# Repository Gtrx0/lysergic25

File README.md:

# Lysergic 25
5x5 Macropad PCB

# [Layout](http://www.keyboard-layout-editor.com/#/gists/2997f919e892d07fd131f2b731a871e9)

## Features
* In-switch LED support.
* Individually addressible RGB underglow provided by 8 separate WS2812B LEDs.
* USB micro B to USB type-C converter which works like the one ergodox, so no more ripped off usb ports on your pro micro.
* Compatible with Cherry MX ALPS and Kailh CHOC switches. 
* Pro Micro microcontroller for easy diy assembly.
* USB ESD protection circuit.
* 0805 SMD and through hole Diode/resistor compatibility for ease of assembly.

## Warning
KiCad 5 or above is needed to open this project. KiCad 4 or below won't work.

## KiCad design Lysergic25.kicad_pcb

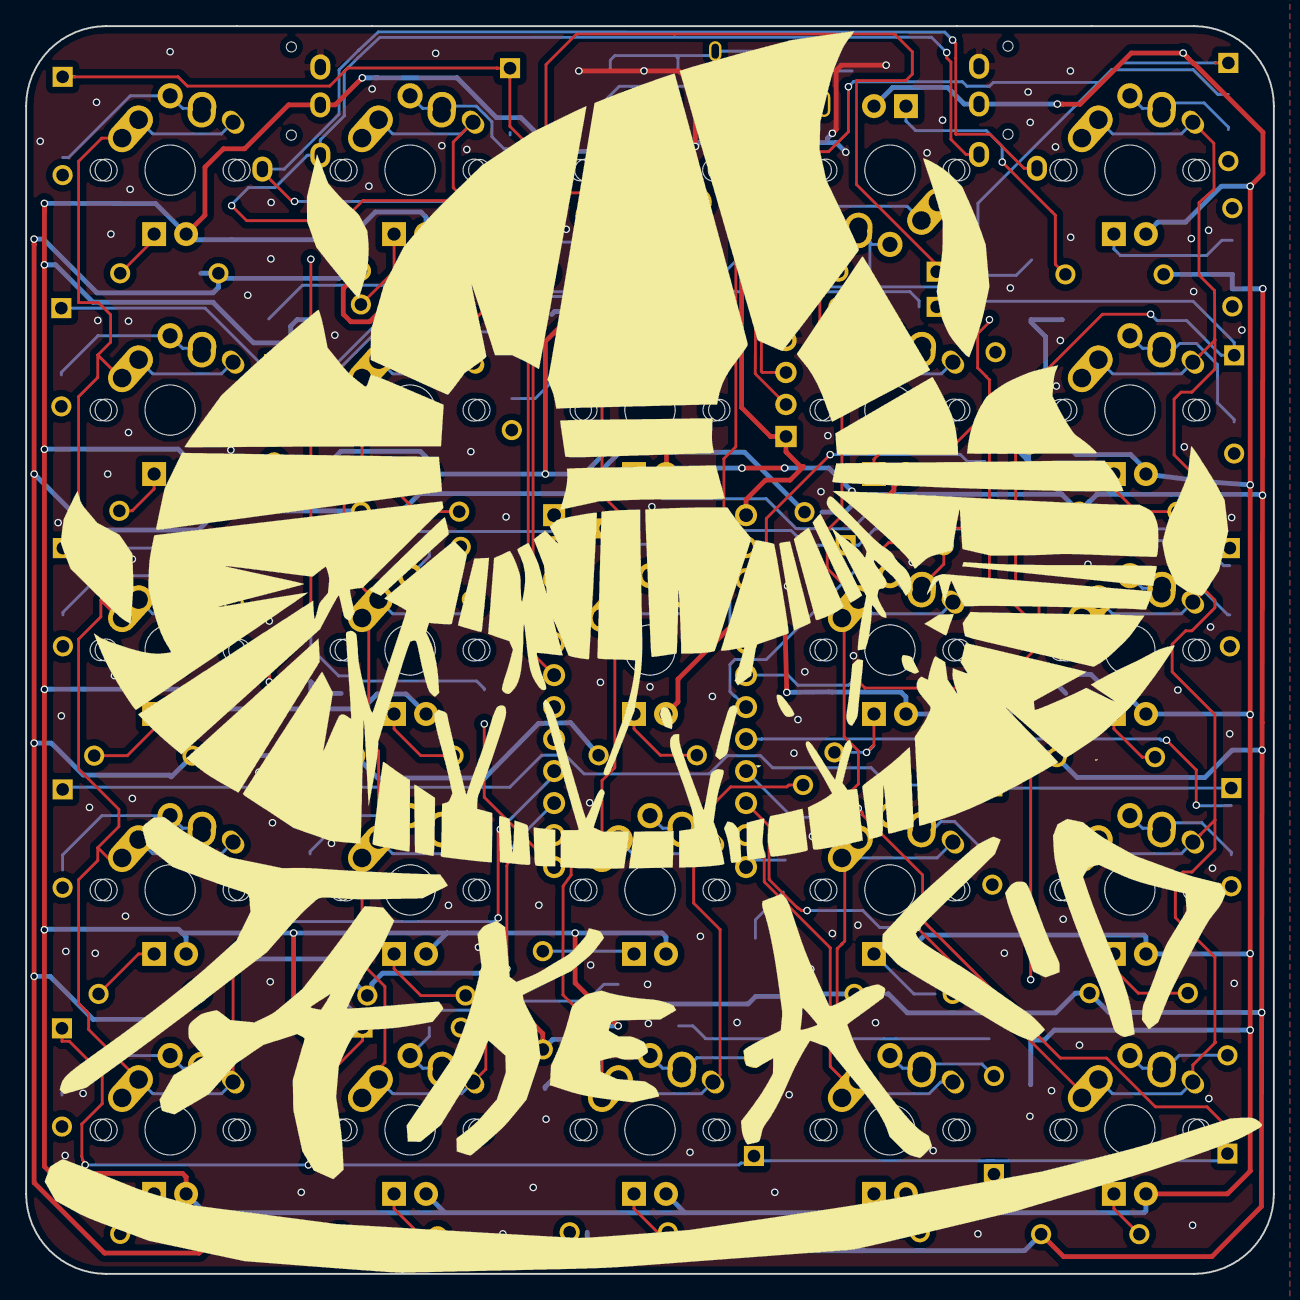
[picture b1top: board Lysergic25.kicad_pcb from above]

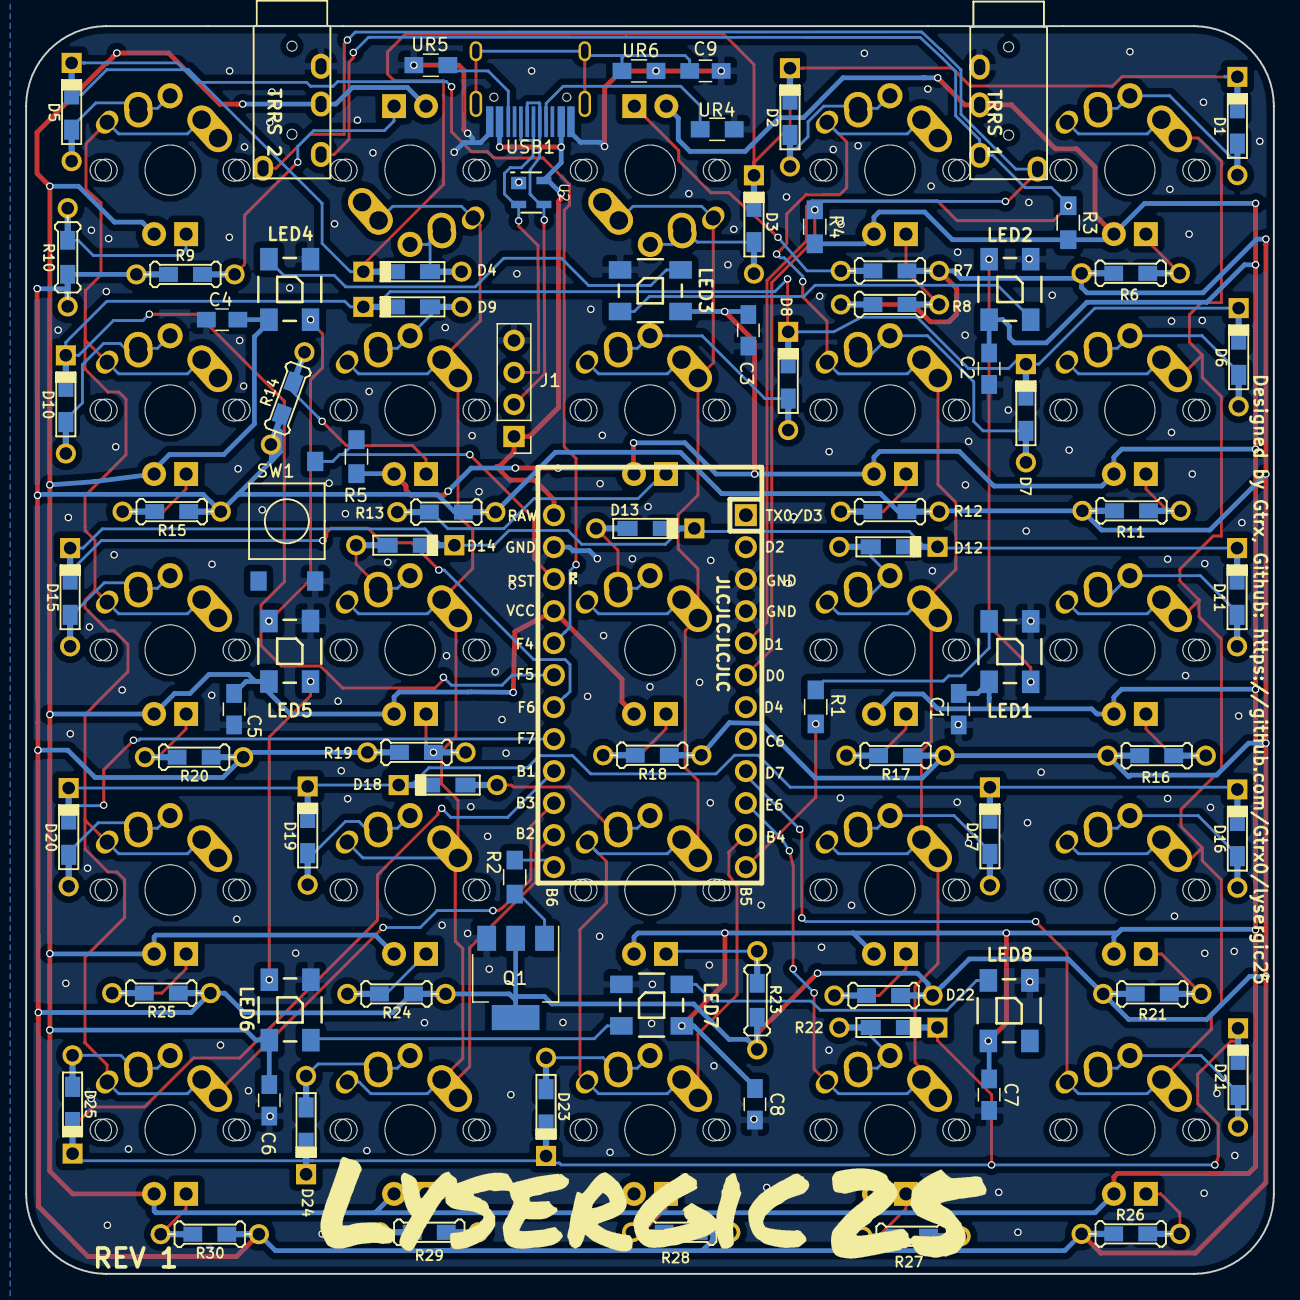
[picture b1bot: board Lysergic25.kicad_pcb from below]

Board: 2 copper layers, 99.1 x 99.1 mm, 108 parts (31 on the bottom side), 83 nets.

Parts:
C1, C2, C3, C4, C5, C6, C7, C8: 0.1uF; C_0805_HandSoldering
C9: 4.7uF; C_0805_HandSoldering
D1, D2, D3, D4, D5, D6, D7, D8, D9, D10, D11, D12, D13, D14, D15, D16, D17, D18, D19, D20, D21, D22, D23, D24, D25: D; Diode-Hybrid-Back
J1: Breakout; Pin_Header_Straight_1x04_Pitch2.54mm
LED1, LED2, LED3, LED4, LED5, LED6, LED7, LED8: WS2812B
MX1, MX2, MX3, MX4, MX5, MX6, MX7, MX8, MX9, MX10, MX11, MX12, MX14, MX15, MX16, MX17, MX18, MX19, MX20, MX21, MX22, MX23, MX24, MX25: MX-1U; MX-1U-FLIPPED
MX13: MX-1U; MX-1U-FLIPPED_No_Hole
Q1: Q_NPN_BCE; SOT-223-3_TabPin2
R1: 470; R_0805_HandSoldering
R2: 1.5k; R_0805_HandSoldering
R3, R4: 2.2K; R_0805_HandSoldering
R5: 100k; R_0805_HandSoldering
R6, R7, R8, R9, R10, R11, R12, R13, R14, R15, R16, R17, R18, R19, R20, R21, R22, R23, R24, R25, R26, R27, R28, R29, R30: R; Resistor-Hybrid-Back
SW1: SW_PUSH; CandK_6x6mm_Tactile
Trrs1, Trrs2: Audio-Jack-4; TRRS-PJ-320A
U1: Pro_Micro; ArduinoProMicro
U2: PRTR5V0U2X; SOT143B
UR4, UR5: 5.1K; R_0805_HandSoldering
UR6: 1M; R_0805_HandSoldering
USB1: HRO-TYPE-C-31-M-12; HRO-TYPE-C-31-M-12-HandSoldering

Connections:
+5V: J1.1, U1.24, U2.4, USB1.2, USB1.11
COL0: MX1.1, MX6.1, MX11.1, MX16.1, MX21.1, U1.9
COL1: MX2.1, MX7.1, MX12.1, MX17.1, MX22.1, U1.10
COL2: MX3.1, MX8.1, MX13.1, MX18.1, MX23.1, U1.11
COL3: MX4.1, MX9.1, MX14.1, MX19.1, MX24.1, U1.14
COL4: MX5.1, MX10.1, MX15.1, MX20.1, MX25.1, U1.15
D+: J1.3, U2.2, USB1.6, USB1.8
D-: J1.2, U2.3, USB1.5, USB1.7
GND: C1.2, C2.2, C3.2, C4.2, C5.2, C6.2, C7.2, C8.2, C9.2, J1.4, LED1.3, LED2.3, LED3.3, LED4.3, LED5.3, LED6.3, LED7.3, LED8.3, Q1.3, SW1.2, Trrs1.4, Trrs2.4, U1.3, U1.4, U1.23, U2.1, UR4.1, UR5.2, UR6.1, USB1.1, USB1.12
LEDGND: Q1.2, R6.2, R7.2, R8.2, R9.2, R10.2, R11.2, R12.2, R13.2, R14.2, R15.2, R16.2, R17.2, R18.2, R19.2, R20.2, R21.2, R22.2, R23.2, R24.2, R25.2, R26.2, R27.2, R28.2, R29.2, R30.2
unnamed: C9.1, UR6.2, USB1.13
unnamed: D1.2, MX1.2
unnamed: D2.2, MX2.2
unnamed: D3.2, MX3.2
unnamed: D4.2, MX4.2
unnamed: D5.2, MX5.2
unnamed: D6.2, MX6.2
unnamed: D7.2, MX7.2
unnamed: D8.2, MX8.2
unnamed: D9.2, MX9.2
unnamed: D10.2, MX10.2
unnamed: D11.2, MX11.2
unnamed: D12.2, MX12.2
unnamed: D13.2, MX13.2
unnamed: D14.2, MX14.2
unnamed: D15.2, MX15.2
unnamed: D16.2, MX16.2
unnamed: D17.2, MX17.2
unnamed: D18.2, MX18.2
unnamed: D19.2, MX19.2
unnamed: D20.2, MX20.2
unnamed: D21.2, MX21.2
unnamed: D22.2, MX22.2
unnamed: D23.2, MX23.2
unnamed: D24.2, MX24.2
unnamed: D25.2, MX25.2
unnamed: LED1.2, LED2.4
unnamed: LED1.4, R1.2
unnamed: LED2.2, LED3.4
unnamed: LED3.2, LED4.4
unnamed: LED4.2, LED5.4
unnamed: LED5.2, LED6.4
unnamed: LED6.2, LED7.4
unnamed: LED7.2, LED8.4
unnamed: MX1.4, R6.1
unnamed: MX2.4, R7.1
unnamed: MX3.4, R8.1
unnamed: MX4.4, R9.1
unnamed: MX5.4, R10.1
unnamed: MX6.4, R11.1
unnamed: MX7.4, R12.1
unnamed: MX8.4, R13.1
unnamed: MX9.4, R14.1
unnamed: MX10.4, R15.1
unnamed: MX11.4, R16.1
unnamed: MX12.4, R17.1
unnamed: MX13.4, R18.1
unnamed: MX14.4, R19.1
unnamed: MX15.4, R20.1
unnamed: MX16.4, R21.1
unnamed: MX17.4, R22.1
unnamed: MX18.4, R23.1
unnamed: MX19.4, R24.1
unnamed: MX20.4, R25.1
unnamed: MX21.4, R26.1
unnamed: MX22.4, R27.1
unnamed: MX23.4, R28.1
unnamed: MX24.4, R29.1
unnamed: MX25.4, R30.1
unnamed: Q1.1, R2.1
unnamed: R5.2, SW1.1, U1.22
unnamed: UR4.2, USB1.4
unnamed: UR5.1, USB1.10
PWMIN: R2.2, U1.13
RGBIN: R1.1, U1.12
ROW0: D1.1, D2.1, D3.1, D4.1, D5.1, U1.20
ROW1: D6.1, D7.1, D8.1, D9.1, D10.1, U1.19
ROW2: D11.1, D12.1, D13.1, D14.1, D15.1, U1.18
ROW3: D16.1, D17.1, D18.1, D19.1, D20.1, U1.17
ROW4: D21.1, D22.1, D23.1, D24.1, D25.1, U1.16
SCL: R4.1, Trrs1.1, Trrs2.1, U1.6
SDA: R3.1, Trrs1.2, Trrs2.2, U1.5
VCC: C1.1, C2.1, C3.1, C4.1, C5.1, C6.1, C7.1, C8.1, LED1.1, LED2.1, LED3.1, LED4.1, LED5.1, LED6.1, LED7.1, LED8.1, MX1.3, MX2.3, MX3.3, MX4.3, MX5.3, MX6.3, MX7.3, MX8.3, MX9.3, MX10.3, MX11.3, MX12.3, MX13.3, MX14.3, MX15.3, MX16.3, MX17.3, MX18.3, MX19.3, MX20.3, MX21.3, MX22.3, MX23.3, MX24.3, MX25.3, R3.2, R4.2, R5.1, Trrs1.3, Trrs2.3, U1.21

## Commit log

2018-08-20 Lysergic25
2018-08-20 Readme updated
2018-08-21 Plate and logo changes
2018-08-23 plate
